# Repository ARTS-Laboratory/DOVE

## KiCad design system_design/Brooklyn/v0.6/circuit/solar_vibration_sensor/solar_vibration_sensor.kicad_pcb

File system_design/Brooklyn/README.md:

# Brooklyn
Designed for modal analysis using a network of sensors.

## Version 0.1.0
1. Joud's Work
1. Basic package with wireless control. 

## Version 0.2.0
1. Ryan's Work
1. Focused on reducing package footprint while improving manufacturability.
1. Creating a stable package with options for different situations.

## Version 0.3.0
1. Ryan's Work
1. Same base package but includes RF and RTC for wireless synchronization.

## Version 0.4.0
1. Ryan's Work
1. Focused on improving the RF functionality.
1. More organized PCB.

## Version 0.5.0
1. Ryan's Work
1. Focused on multilayered PCB with the same base package.

## Version 0.6.0
1. Joud, Asif & Fardin's Work
1. Focused on adding the Solar System to the sensor, integrating BMS and RTC based shutdown.

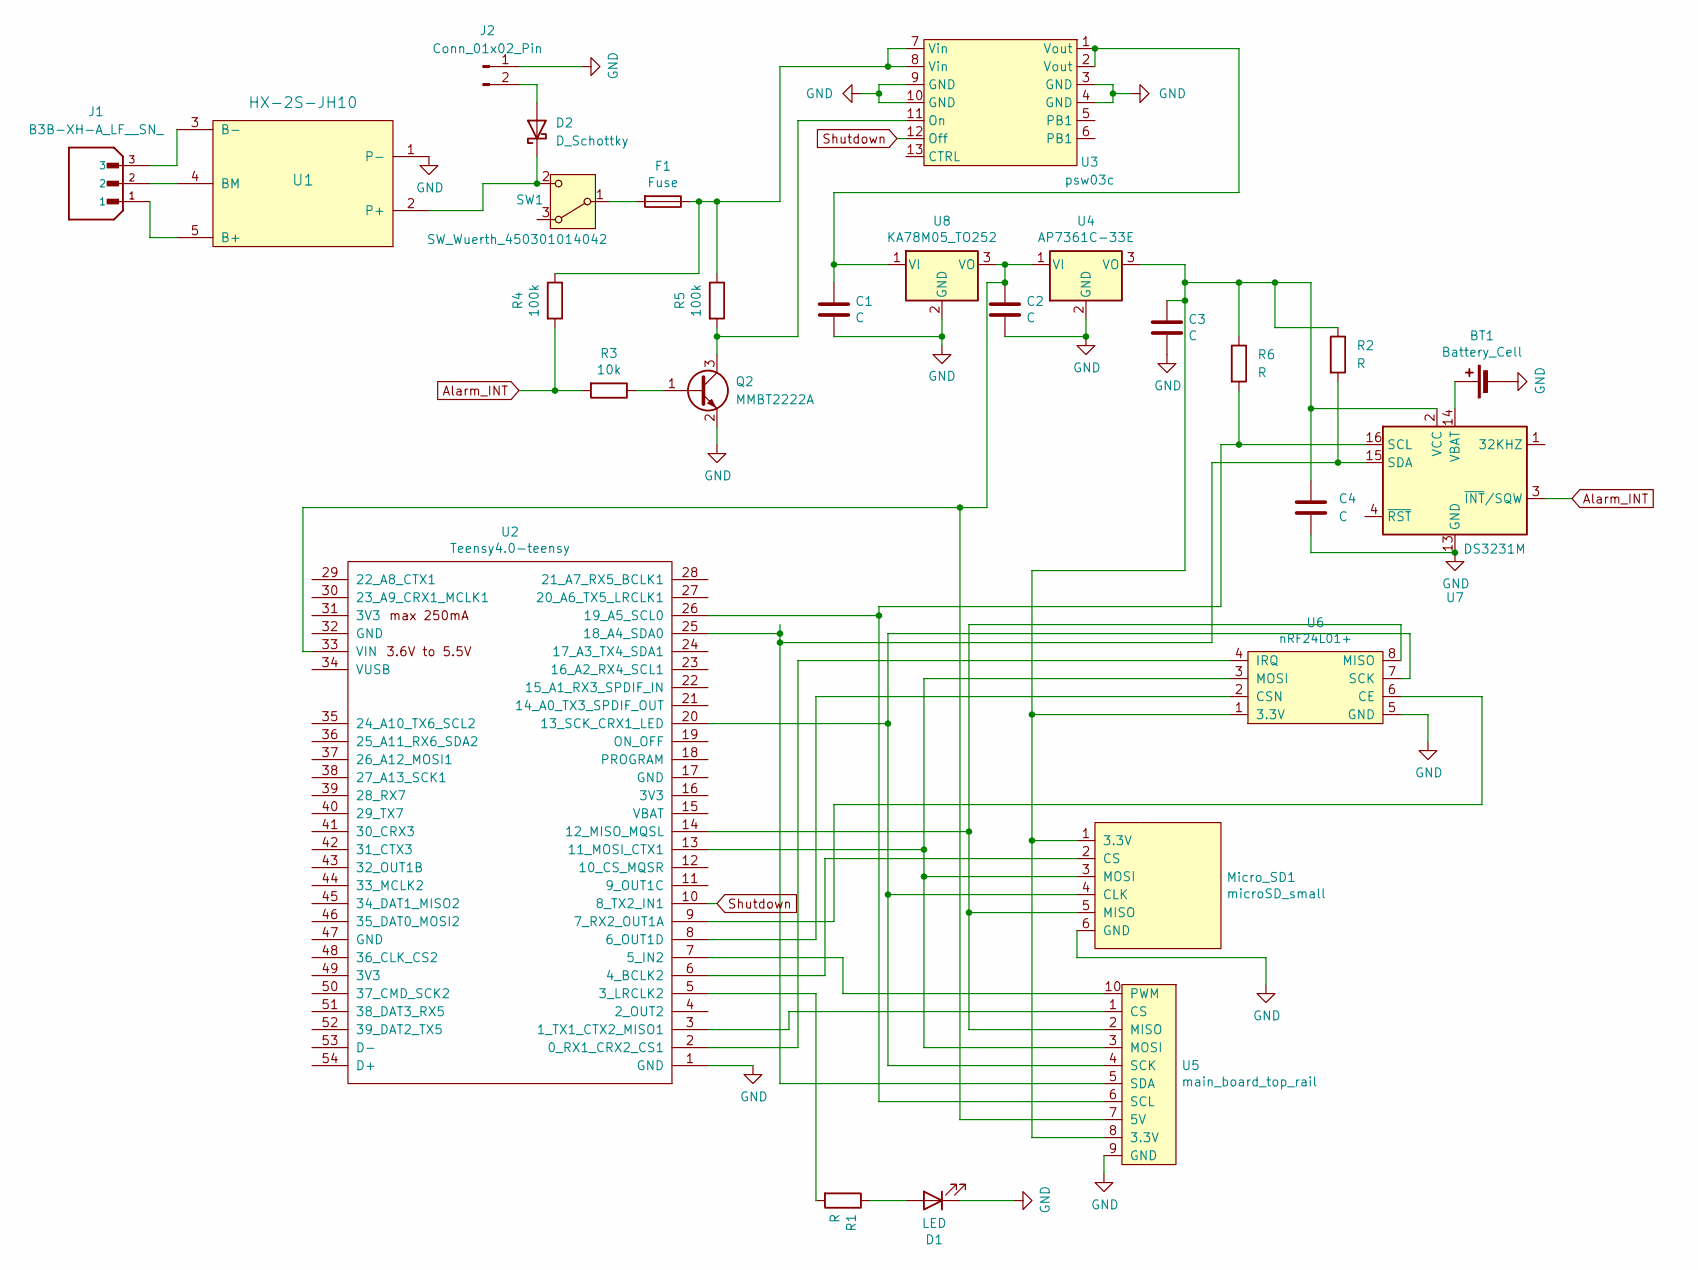
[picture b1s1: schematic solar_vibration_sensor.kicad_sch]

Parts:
BT1: Battery_Cell; BT1
C1, C2, C3, C4: C; C_1206_3216Metric_Pad1.33x1.80mm_HandSolder
D1: LED; LED_D3.0mm
D2: D_Schottky; D_1206_3216Metric
F1: Fuse; C_1206_3216Metric_Pad1.33x1.80mm_HandSolder
J1: B3B-XH-A_LF__SN_; PARTREV 7/4/21
J2: Conn_01x02_Pin; PinHeader_1x02_P2.54mm_Vertical
Micro_SD1: microSD_small; sdcard
Q2: MMBT2222A; SOT-23
R1: R; R_1206_3216Metric_Pad1.30x1.75mm_HandSolder
R2, R6: R; C_1206_3216Metric_Pad1.33x1.80mm_HandSolder
R3: 10k; C_1206_3216Metric_Pad1.33x1.80mm_HandSolder
R4, R5: 100k; C_1206_3216Metric_Pad1.33x1.80mm_HandSolder
SW1: SW_Wuerth_450301014042; SW_Slide-03_Wuerth-WS-SLTV_10x2.5x6.4_P2.54mm
U1: HX-2S-JH10; hx2sjh10
U2: Teensy4.0-teensy; arduino
U3: psw03c; Untitled
U4: AP7361C-33E; SOT-223-3_TabPin2
U5: main_board_top_rail
U6: nRF24L01+; nrf24L01
U7: DS3231M; SOIC-16W_7.5x10.3mm_P1.27mm
U8: KA78M05_TO252; SOT-223-3_TabPin2

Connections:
Alarm_INT: R3.2, R4.2, U7.3 (~INT/SQW)
GND: BT1.2 (-), C1.2, C2.2, C3.2, C4.2, D1.1 (K), J2.1, Micro_SD1.6 (GND), Q2.2 (E), U1.1 (P-), U2.1 (GND), U3.3 (GND), U3.4 (GND), U3.9 (GND), U3.10 (GND), U4.2 (GND), U5.9 (GND), U6.5 (GND), U7.5 (GND), U7.6 (GND), U7.7 (GND), U7.8 (GND), U7.9 (GND), U7.10 (GND), U7.11 (GND), U7.12 (GND), U7.13 (GND), U8.2 (GND)
unnamed: BT1.1 (+), U7.14 (VBAT)
unnamed: D1.2 (A), R1.1
unnamed: D2.2 (A), J2.2
unnamed: D2.1 (K), SW1.2 (C), U1.2 (P+)
unnamed: F1.1, R4.1, R5.1, U3.7 (Vin), U3.8 (Vin)
unnamed: C3.1, C4.1, Micro_SD1.1 (3.3V), R2.1, R6.1, U4.3 (VO), U5.8 (3.3V), U6.1 (3.3V), U7.2 (VCC)
unnamed: Micro_SD1.4 (CLK), U2.20 (13_SCK_CRX1_LED), U5.4 (SCK), U6.7 (SCK)
unnamed: Micro_SD1.2 (CS), U2.6 (4_BCLK2)
unnamed: Micro_SD1.5 (MISO), U2.14 (12_MISO_MQSL), U5.2 (MISO), U6.8 (MISO)
unnamed: Micro_SD1.3 (MOSI), U2.13 (11_MOSI_CTX1), U5.3 (MOSI), U6.3 (MOSI)
unnamed: Q2.1 (B), R3.1
unnamed: Q2.3 (C), R5.2, U3.11 (On)
unnamed: F1.2, SW1.1 (B)
unnamed: J1.1, U1.5 (B+)
unnamed: J1.3, U1.3 (B-)
unnamed: J1.2, U1.4 (BM)
unnamed: U2.2 (0_RX1_CRX2_CS1), U6.4 (IRQ)
unnamed: U2.3 (1_TX1_CTX2_MISO1), U5.1 (CS)
unnamed: R1.2, U2.5 (3_LRCLK2)
unnamed: U2.7 (5_IN2), U5.10 (PWM)
unnamed: U2.8 (6_OUT1D), U6.2 (CSN)
unnamed: U2.9 (7_RX2_OUT1A), U6.6 (CE)
unnamed: R2.2, U2.25 (18_A4_SDA0), U5.5 (SDA), U7.15 (SDA)
unnamed: R6.2, U2.26 (19_A5_SCL0), U5.6 (SCL), U7.16 (SCL)
unnamed: C2.1, U2.33 (VIN), U4.1 (VI), U5.7 (5V), U8.3 (VO)
unnamed: C1.1, U3.1 (Vout), U3.2 (Vout), U8.1 (VI)
Shutdown: U2.10 (8_TX2_IN1), U3.12 (Off)

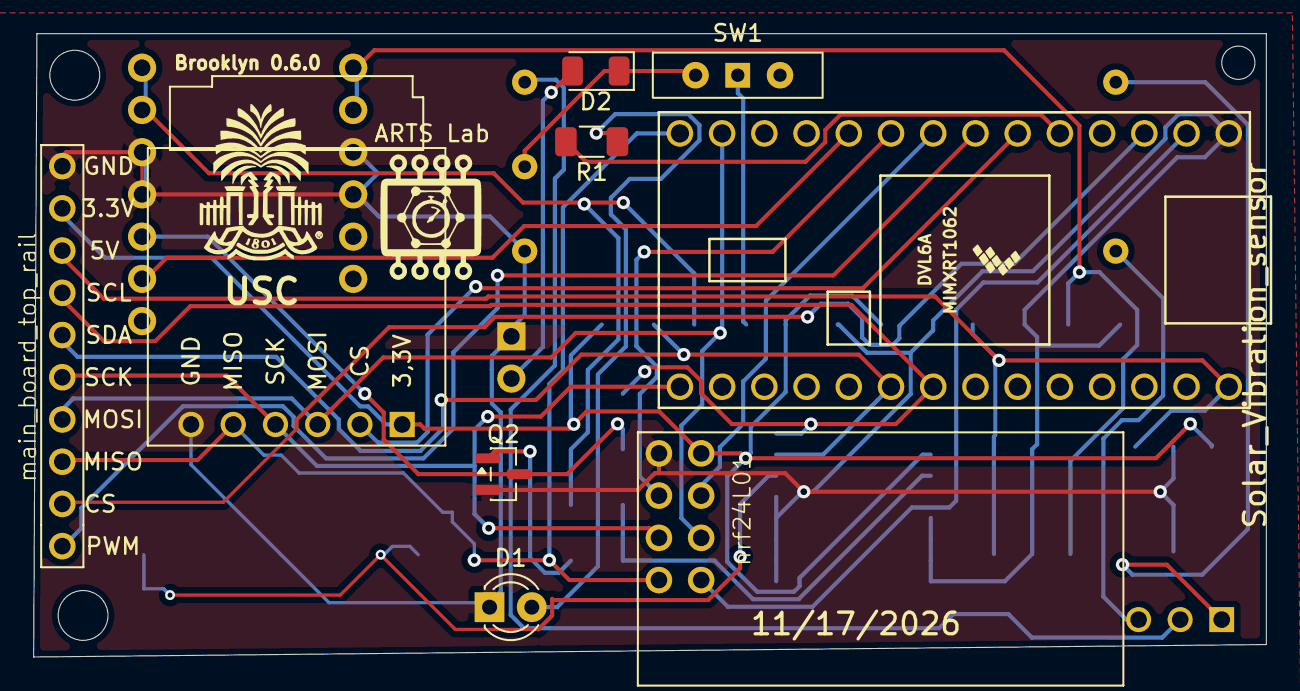
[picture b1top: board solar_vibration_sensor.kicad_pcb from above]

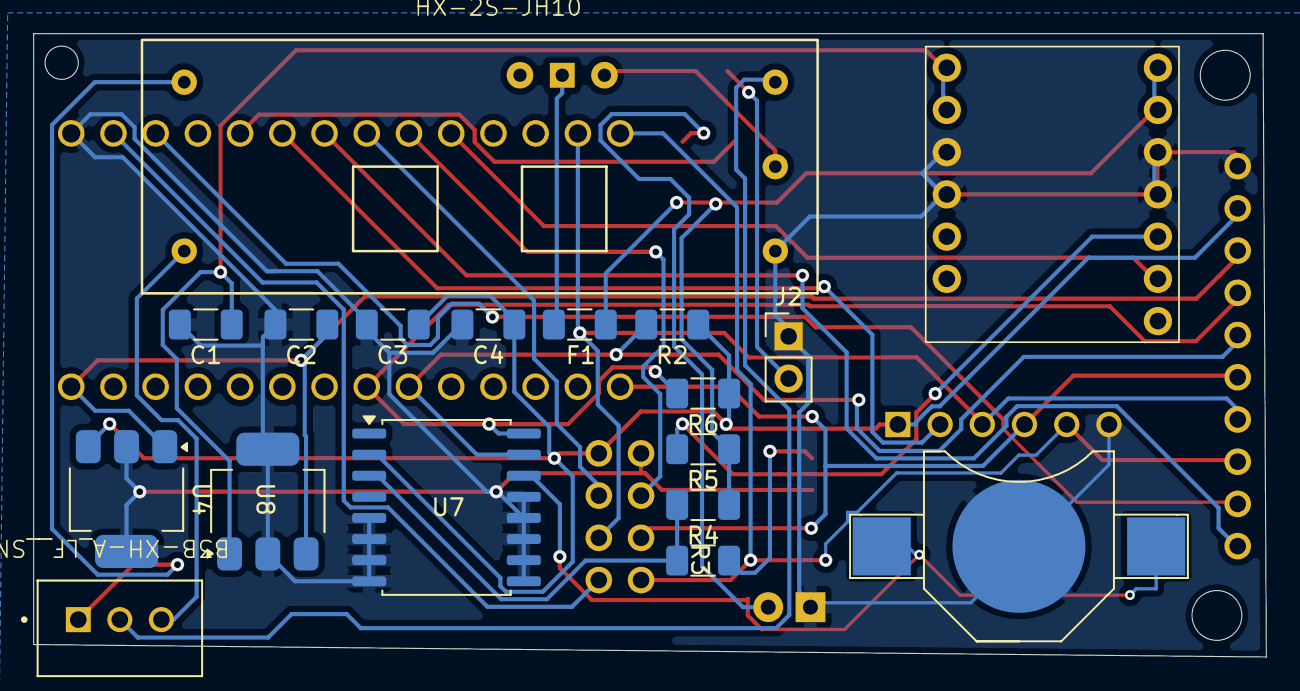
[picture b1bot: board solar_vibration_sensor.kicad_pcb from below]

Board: 2 copper layers, 74.2 x 37.5 mm, 29 parts (20 on the bottom side), 29 nets.

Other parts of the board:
ARTS Lab: LOGO
USC: UofSC; LOGO
